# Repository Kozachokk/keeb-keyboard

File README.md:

# keeb-keyboard
Custom keyboard for keeb hackclub

So I built a keyboard from scratch, including the pcb and the case themselves.
I started this project as sort of an introduction to electrical stuff and pcb designing.
During my journey, I learned a lot about pcb designing, wiring, placing vias, creating schematics. I also learned to do keyboard layout, how to use kicad and onshape, where I learned how to create keyboard cases

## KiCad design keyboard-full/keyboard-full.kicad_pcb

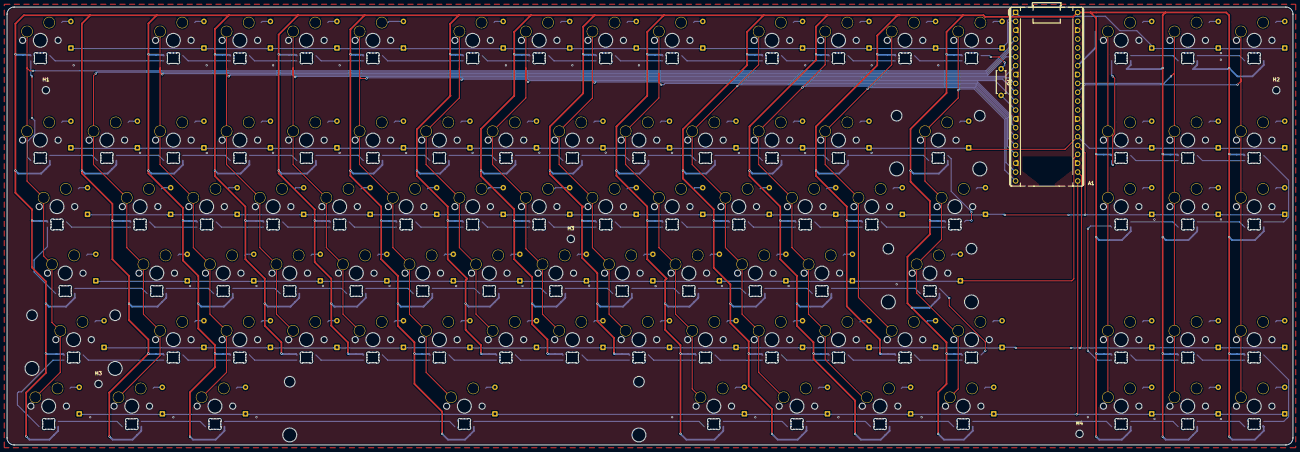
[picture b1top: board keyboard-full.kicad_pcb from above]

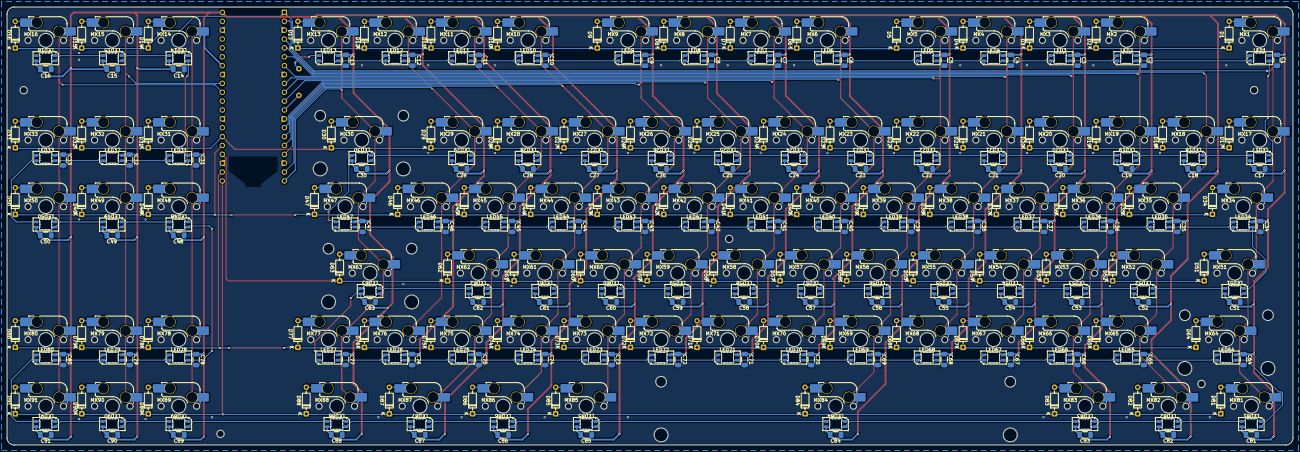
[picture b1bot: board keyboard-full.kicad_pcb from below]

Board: 2 copper layers, 368.3 x 125.4 mm, 375 parts (364 on the bottom side), 208 nets.

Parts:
A1: RaspberryPi_Pico; RaspberryPi_Pico_Common_THT
C1, C2, C3, C4, C5, C6, C7, C8, C9, C10, C11, C12, C13, C14, C15, C16, C17, C18, C19, C20, C21, C22, C23, C24, C25, C26, C27, C28, C29, C30, C31, C32, C33, C34, C35, C36, C37, C38, C39, C40, C41, C42, C43, C44, C45, C46, C47, C48, C49, C50, C51, C52, C53, C54, C55, C56, C57, C58, C59, C60, C61, C62, C63, C64, C65, C66, C67, C68, C69, C70, C71, C72, C73, C74, C75, C76, C77, C78, C79, C80, C81, C82, C83, C84, C85, C86, C87, C88, C89, C90, C91: 0.1uF; C_1206_3216Metric_Pad1.33x1.80mm_HandSolder
D1, D2, D3, D4, D5, D6, D7, D8, D9, D10, D11, D12, D13, D14, D15, D16, D17, D18, D19, D20, D21, D22, D23, D24, D25, D26, D27, D28, D29, D30, D31, D32, D33, D34, D35, D36, D37, D38, D39, D40, D41, D42, D43, D44, D45, D46, D47, D48, D49, D50, D51, D52, D53, D54, D55, D56, D57, D58, D59, D60, D61, D62, D63, D64, D65, D66, D67, D68, D69, D70, D71, D72, D73, D74, D75, D76, D77, D78, D79, D80, D81, D82, D83, D84, D85, D86, D87, D88, D89, D90, D91: 1N4148; D_DO-35_SOD27_P7.62mm_Horizontal
H1, H2, H3, H3#2, H4: MountingHole; MountingHole_2.1mm
LED1, LED2, LED3, LED4, LED5, LED6, LED7, LED8, LED9, LED10, LED11, LED12, LED13, LED14, LED15, LED16, LED17, LED18, LED19, LED20, LED21, LED22, LED23, LED24, LED25, LED26, LED27, LED28, LED29, LED30, LED31, LED32, LED33, LED34, LED35, LED36, LED37, LED38, LED39, LED40, LED41, LED42, LED43, LED44, LED45, LED46, LED47, LED48, LED49, LED50, LED51, LED52, LED53, LED54, LED55, LED56, LED57, LED58, LED59, LED60, LED61, LED62, LED63, LED64, LED65, LED66, LED67, LED68, LED69, LED70, LED71, LED72, LED73, LED74, LED75, LED76, LED77, LED78, LED79, LED80, LED81, LED82, LED83, LED84, LED85, LED86, LED87, LED88, LED89, LED90, LED91: SK6812MINI-E; LED_SK6812MINI-E_3.2x2.8mm_P1.5mm_ReverseMount
MX1, MX2, MX3, MX4, MX5, MX6, MX7, MX8, MX9, MX10, MX11, MX12, MX13, MX14, MX15, MX16, MX17, MX18, MX19, MX20, MX21, MX22, MX23, MX24, MX25, MX26, MX27, MX28, MX29, MX30, MX31, MX32, MX33, MX35, MX36, MX37, MX38, MX39, MX40, MX41, MX42, MX43, MX44, MX45, MX46, MX48, MX49, MX50, MX52, MX53, MX54, MX55, MX56, MX57, MX58, MX59, MX60, MX61, MX62, MX63, MX64, MX65, MX66, MX67, MX68, MX69, MX70, MX71, MX72, MX73, MX74, MX75, MX76, MX77, MX78, MX79, MX80, MX89, MX90, MX91: MX_SW_HS; SW_MX_HS_CPG151101S11_1u
MX34, MX47: MX_SW_HS; SW_MX_HS_CPG151101S11_1.5u
MX51: MX_SW_HS; SW_MX_HS_CPG151101S11_1.75u
MX81, MX82, MX83, MX84, MX85, MX86, MX87, MX88: MX_SW_HS; SW_MX_HS_CPG151101S11_1.25u
R1: R470; R_Axial_DIN0207_L6.3mm_D2.5mm_P7.62mm_Horizontal
S1: MX_stab; STAB_MX_6.25u
S2, S3: MX_stab; STAB_MX_2u
S4: MX_stab; STAB_MX_2.25u

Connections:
+5V: A1.40 (VBUS), C1.1, C2.1, C3.1, C4.1, C5.1, C6.1, C7.1, C8.1, C9.1, C10.1, C11.1, C12.1, C13.1, C14.1, C15.1, C16.1, C17.1, C18.1, C19.1, C20.1, C21.1, C22.1, C23.1, C24.1, C25.1, C26.1, C27.1, C28.1, C29.1, C30.1, C31.1, C32.1, C33.1, C34.1, C35.1, C36.1, C37.1, C38.1, C39.1, C40.1, C41.1, C42.1, C43.1, C44.1, C45.1, C46.1, C47.1, C48.1, C49.1, C50.1, C51.1, C52.1, C53.1, C54.1, C55.1, C56.1, C57.1, C58.1, C59.1, C60.1, C61.1, C62.1, C63.1, C64.1, C65.1, C66.1, C67.1, C68.1, C69.1, C70.1, C71.1, C72.1, C73.1, C74.1, C75.1, C76.1, C77.1, C78.1, C79.1, C80.1, C81.1, C82.1, C83.1, C84.1, C85.1, C86.1, C87.1, C88.1, C89.1, C90.1, C91.1, LED1.3 (VDD), LED2.3 (VDD), LED3.3 (VDD), LED4.3 (VDD), LED5.3 (VDD), LED6.3 (VDD), LED7.3 (VDD), LED8.3 (VDD), LED9.3 (VDD), LED10.3 (VDD), LED11.3 (VDD), LED12.3 (VDD), LED13.3 (VDD), LED14.3 (VDD), LED15.3 (VDD), LED16.3 (VDD), LED17.3 (VDD), LED18.3 (VDD), LED19.3 (VDD), LED20.3 (VDD), LED21.3 (VDD), LED22.3 (VDD), LED23.3 (VDD), LED24.3 (VDD), LED25.3 (VDD), LED26.3 (VDD), LED27.3 (VDD), LED28.3 (VDD), LED29.3 (VDD), LED30.3 (VDD), LED31.3 (VDD), LED32.3 (VDD), LED33.3 (VDD), LED34.3 (VDD), LED35.3 (VDD), LED36.3 (VDD), LED37.3 (VDD), LED38.3 (VDD), LED39.3 (VDD), LED40.3 (VDD), LED41.3 (VDD), LED42.3 (VDD), LED43.3 (VDD), LED44.3 (VDD), LED45.3 (VDD), LED46.3 (VDD), LED47.3 (VDD), LED48.3 (VDD), LED49.3 (VDD), LED50.3 (VDD), LED51.3 (VDD), LED52.3 (VDD), LED53.3 (VDD), LED54.3 (VDD), LED55.3 (VDD), LED56.3 (VDD), LED57.3 (VDD), LED58.3 (VDD), LED59.3 (VDD), LED60.3 (VDD), LED61.3 (VDD), LED62.3 (VDD), LED63.3 (VDD), LED64.3 (VDD), LED65.3 (VDD), LED66.3 (VDD), LED67.3 (VDD), LED68.3 (VDD), LED69.3 (VDD), LED70.3 (VDD), LED71.3 (VDD), LED72.3 (VDD), LED73.3 (VDD), LED74.3 (VDD), LED75.3 (VDD), LED76.3 (VDD), LED77.3 (VDD), LED78.3 (VDD), LED79.3 (VDD), LED80.3 (VDD), LED81.3 (VDD), LED82.3 (VDD), LED83.3 (VDD), LED84.3 (VDD), LED85.3 (VDD), LED86.3 (VDD), LED87.3 (VDD), LED88.3 (VDD), LED89.3 (VDD), LED90.3 (VDD), LED91.3 (VDD)
/Col0: A1.2 (GPIO1), MX1.1, MX17.1, MX34.1, MX51.1, MX64.1, MX81.1
/Col1: A1.4 (GPIO2), MX18.1, MX35.1, MX52.1, MX65.1, MX82.1
/Col2: A1.5 (GPIO3), MX2.1, MX19.1, MX36.1, MX53.1, MX66.1, MX83.1
/Col3: A1.6 (GPIO4), MX3.1, MX20.1, MX37.1, MX54.1, MX67.1
/Col4: A1.7 (GPIO5), MX4.1, MX21.1, MX38.1, MX55.1, MX68.1
/Col5: A1.9 (GPIO6), MX5.1, MX22.1, MX39.1, MX56.1, MX69.1, MX84.1
/Col6: A1.10 (GPIO7), MX6.1, MX23.1, MX40.1, MX57.1, MX70.1
/Col7: A1.11 (GPIO8), MX7.1, MX24.1, MX41.1, MX58.1, MX71.1
/Col8: A1.14 (GPIO10), MX8.1, MX25.1, MX42.1, MX59.1, MX72.1
/Col9: A1.15 (GPIO11), MX9.1, MX26.1, MX43.1, MX60.1, MX73.1, MX85.1
/Col10: A1.16 (GPIO12), MX10.1, MX27.1, MX44.1, MX61.1, MX74.1, MX86.1
/Col11: A1.17 (GPIO13), MX11.1, MX28.1, MX45.1, MX62.1, MX75.1, MX87.1
/Col12: A1.19 (GPIO14), MX12.1, MX29.1, MX46.1, MX76.1
/Col13: A1.20 (GPIO15), MX13.1, MX30.1, MX47.1, MX63.1, MX77.1, MX88.1
/Col14: A1.34 (GPIO28_ADC2), MX14.1, MX31.1, MX48.1, MX78.1, MX89.1
/Col15: A1.32 (GPIO27_ADC1), MX15.1, MX32.1, MX49.1, MX79.1, MX90.1
/Col16: A1.31 (GPIO26_ADC0), MX16.1, MX33.1, MX50.1, MX80.1, MX91.1
/LED: A1.12 (GPIO9), R1.2
/Row0: A1.1 (GPIO0), D1.1 (K), D2.1 (K), D3.1 (K), D4.1 (K), D5.1 (K), D6.1 (K), D7.1 (K), D8.1 (K), D9.1 (K), D10.1 (K), D11.1 (K), D12.1 (K), D13.1 (K), D14.1 (K), D15.1 (K), D16.1 (K)
/Row1: A1.26 (GPIO20), D17.1 (K), D18.1 (K), D19.1 (K), D20.1 (K), D21.1 (K), D22.1 (K), D23.1 (K), D24.1 (K), D25.1 (K), D26.1 (K), D27.1 (K), D28.1 (K), D29.1 (K), D30.1 (K), D31.1 (K), D32.1 (K), D33.1 (K)
/Row2: A1.25 (GPIO19), D34.1 (K), D35.1 (K), D36.1 (K), D37.1 (K), D38.1 (K), D39.1 (K), D40.1 (K), D41.1 (K), D42.1 (K), D43.1 (K), D44.1 (K), D45.1 (K), D46.1 (K), D47.1 (K), D48.1 (K), D49.1 (K), D50.1 (K)
/Row3: A1.24 (GPIO18), D51.1 (K), D52.1 (K), D53.1 (K), D54.1 (K), D55.1 (K), D56.1 (K), D57.1 (K), D58.1 (K), D59.1 (K), D60.1 (K), D61.1 (K), D62.1 (K), D63.1 (K)
/Row4: A1.22 (GPIO17), D64.1 (K), D65.1 (K), D66.1 (K), D67.1 (K), D68.1 (K), D69.1 (K), D70.1 (K), D71.1 (K), D72.1 (K), D73.1 (K), D74.1 (K), D75.1 (K), D76.1 (K), D77.1 (K), D78.1 (K), D79.1 (K), D80.1 (K)
/Row5: A1.21 (GPIO16), D81.1 (K), D82.1 (K), D83.1 (K), D84.1 (K), D85.1 (K), D86.1 (K), D87.1 (K), D88.1 (K), D89.1 (K), D90.1 (K), D91.1 (K)
GND: A1.3 (GND), A1.8 (GND), A1.13 (GND), A1.18 (GND), A1.23 (GND), A1.28 (GND), A1.38 (GND), C1.2, C2.2, C3.2, C4.2, C5.2, C6.2, C7.2, C8.2, C9.2, C10.2, C11.2, C12.2, C13.2, C14.2, C15.2, C16.2, C17.2, C18.2, C19.2, C20.2, C21.2, C22.2, C23.2, C24.2, C26.2, C27.2, C28.2, C29.2, C30.2, C31.2, C32.2, C33.2, C34.2, C35.2, C36.2, C37.2, C38.2, C39.2, C40.2, C41.2, C42.2, C43.2, C44.2, C45.2, C46.2, C47.2, C48.2, C49.2, C50.2, C51.2, C52.2, C53.2, C54.2, C55.2, C56.2, C57.2, C58.2, C59.2, C60.2, C61.2, C62.2, C63.2, C64.2, C65.2, C66.2, C67.2, C68.2, C69.2, C70.2, C71.2, C72.2, C73.2, C74.2, C75.2, C76.2, C77.2, C78.2, C79.2, C80.2, C81.2, C82.2, C83.2, C84.2, C85.2, C86.2, C87.2, C88.2, C89.2, C90.2, C91.2, LED1.1 (VSS), LED2.1 (VSS), LED3.1 (VSS), LED4.1 (VSS), LED5.1 (VSS), LED6.1 (VSS), LED7.1 (VSS), LED8.1 (VSS), LED9.1 (VSS), LED10.1 (VSS), LED11.1 (VSS), LED12.1 (VSS), LED13.1 (VSS), LED14.1 (VSS), LED15.1 (VSS), LED16.1 (VSS), LED17.1 (VSS), LED18.1 (VSS), LED19.1 (VSS), LED20.1 (VSS), LED21.1 (VSS), LED22.1 (VSS), LED23.1 (VSS), LED24.1 (VSS), LED25.1 (VSS), LED26.1 (VSS), LED27.1 (VSS), LED28.1 (VSS), LED29.1 (VSS), LED30.1 (VSS), LED31.1 (VSS), LED32.1 (VSS), LED33.1 (VSS), LED34.1 (VSS), LED35.1 (VSS), LED36.1 (VSS), LED37.1 (VSS), LED38.1 (VSS), LED39.1 (VSS), LED40.1 (VSS), LED41.1 (VSS), LED42.1 (VSS), LED43.1 (VSS), LED44.1 (VSS), LED45.1 (VSS), LED46.1 (VSS), LED47.1 (VSS), LED48.1 (VSS), LED49.1 (VSS), LED50.1 (VSS), LED51.1 (VSS), LED52.1 (VSS), LED53.1 (VSS), LED54.1 (VSS), LED55.1 (VSS), LED56.1 (VSS), LED57.1 (VSS), LED58.1 (VSS), LED59.1 (VSS), LED60.1 (VSS), LED61.1 (VSS), LED62.1 (VSS), LED63.1 (VSS), LED64.1 (VSS), LED65.1 (VSS), LED66.1 (VSS), LED67.1 (VSS), LED68.1 (VSS), LED69.1 (VSS), LED70.1 (VSS), LED71.1 (VSS), LED72.1 (VSS), LED73.1 (VSS), LED74.1 (VSS), LED75.1 (VSS), LED76.1 (VSS), LED77.1 (VSS), LED78.1 (VSS), LED79.1 (VSS), LED80.1 (VSS), LED81.1 (VSS), LED82.1 (VSS), LED83.1 (VSS), LED84.1 (VSS), LED85.1 (VSS), LED86.1 (VSS), LED87.1 (VSS), LED88.1 (VSS), LED89.1 (VSS), LED90.1 (VSS), LED91.1 (VSS)
unnamed: D1.2 (A), MX1.2
unnamed: D2.2 (A), MX2.2
unnamed: D3.2 (A), MX3.2
unnamed: D4.2 (A), MX4.2
unnamed: D5.2 (A), MX5.2
unnamed: D6.2 (A), MX6.2
unnamed: D7.2 (A), MX7.2
unnamed: D8.2 (A), MX8.2
unnamed: D9.2 (A), MX9.2
unnamed: D10.2 (A), MX10.2
unnamed: D11.2 (A), MX11.2
unnamed: D12.2 (A), MX12.2
unnamed: D13.2 (A), MX13.2
unnamed: D14.2 (A), MX14.2
unnamed: D15.2 (A), MX15.2
unnamed: D16.2 (A), MX16.2
unnamed: D17.2 (A), MX17.2
unnamed: D18.2 (A), MX18.2
unnamed: D19.2 (A), MX19.2
unnamed: D20.2 (A), MX20.2
unnamed: D21.2 (A), MX21.2
unnamed: D22.2 (A), MX22.2
unnamed: D23.2 (A), MX23.2
unnamed: D24.2 (A), MX24.2
unnamed: D25.2 (A), MX25.2
unnamed: D26.2 (A), MX26.2
unnamed: D27.2 (A), MX27.2
unnamed: D28.2 (A), MX28.2
unnamed: D29.2 (A), MX29.2
unnamed: D30.2 (A), MX30.2
unnamed: D31.2 (A), MX31.2
unnamed: D32.2 (A), MX32.2
unnamed: D33.2 (A), MX33.2
unnamed: D34.2 (A), MX34.2
unnamed: D35.2 (A), MX35.2
unnamed: D36.2 (A), MX36.2
unnamed: D37.2 (A), MX37.2
unnamed: D38.2 (A), MX38.2
unnamed: D39.2 (A), MX39.2
unnamed: D40.2 (A), MX40.2
unnamed: D41.2 (A), MX41.2
unnamed: D42.2 (A), MX42.2
unnamed: D43.2 (A), MX43.2
unnamed: D44.2 (A), MX44.2
unnamed: D45.2 (A), MX45.2
unnamed: D46.2 (A), MX46.2
unnamed: D47.2 (A), MX47.2
unnamed: D48.2 (A), MX48.2
unnamed: D49.2 (A), MX49.2
unnamed: D50.2 (A), MX50.2
unnamed: D51.2 (A), MX51.2
unnamed: D52.2 (A), MX52.2
unnamed: D53.2 (A), MX53.2
unnamed: D54.2 (A), MX54.2
unnamed: D55.2 (A), MX55.2
unnamed: D56.2 (A), MX56.2
unnamed: D57.2 (A), MX57.2
unnamed: D58.2 (A), MX58.2
unnamed: D59.2 (A), MX59.2
unnamed: D60.2 (A), MX60.2
unnamed: D61.2 (A), MX61.2
unnamed: D62.2 (A), MX62.2
unnamed: D63.2 (A), MX63.2
unnamed: D64.2 (A), MX64.2
unnamed: D65.2 (A), MX65.2
unnamed: D66.2 (A), MX66.2
unnamed: D67.2 (A), MX67.2
unnamed: D68.2 (A), MX68.2
unnamed: D69.2 (A), MX69.2
unnamed: D70.2 (A), MX70.2
unnamed: D71.2 (A), MX71.2
unnamed: D72.2 (A), MX72.2
unnamed: D73.2 (A), MX73.2
unnamed: D74.2 (A), MX74.2
unnamed: D75.2 (A), MX75.2
unnamed: D76.2 (A), MX76.2
unnamed: D77.2 (A), MX77.2
unnamed: D78.2 (A), MX78.2
unnamed: D79.2 (A), MX79.2
unnamed: D80.2 (A), MX80.2
unnamed: D81.2 (A), MX81.2
unnamed: D82.2 (A), MX82.2
unnamed: D83.2 (A), MX83.2
unnamed: D84.2 (A), MX84.2
unnamed: D85.2 (A), MX85.2
unnamed: D86.2 (A), MX86.2
unnamed: D87.2 (A), MX87.2
unnamed: D88.2 (A), MX88.2
unnamed: D89.2 (A), MX89.2
unnamed: D90.2 (A), MX90.2
unnamed: D91.2 (A), MX91.2
unnamed: LED1.2 (DIN), LED2.4 (DOUT)
unnamed: LED1.4 (DOUT), LED17.2 (DIN)
unnamed: LED2.2 (DIN), LED3.4 (DOUT)
unnamed: LED3.2 (DIN), LED4.4 (DOUT)
unnamed: LED4.2 (DIN), LED5.4 (DOUT)
unnamed: LED5.2 (DIN), LED6.4 (DOUT)
unnamed: LED6.2 (DIN), LED7.4 (DOUT)
unnamed: LED7.2 (DIN), LED8.4 (DOUT)
unnamed: LED8.2 (DIN), LED9.4 (DOUT)
unnamed: LED10.2 (DIN), LED11.4 (DOUT)
unnamed: LED9.2 (DIN), LED10.4 (DOUT)
unnamed: LED11.2 (DIN), LED12.4 (DOUT)
unnamed: LED12.2 (DIN), LED13.4 (DOUT)
unnamed: LED13.2 (DIN), R1.1
unnamed: LED14.2 (DIN), LED31.4 (DOUT)
unnamed: LED14.4 (DOUT), LED15.2 (DIN)
unnamed: LED15.4 (DOUT), LED16.2 (DIN)
unnamed: LED17.4 (DOUT), LED18.2 (DIN)
unnamed: LED18.4 (DOUT), LED19.2 (DIN)
unnamed: LED19.4 (DOUT), LED20.2 (DIN)
unnamed: LED20.4 (DOUT), LED21.2 (DIN)
unnamed: LED21.4 (DOUT), LED22.2 (DIN)
unnamed: LED22.4 (DOUT), LED23.2 (DIN)
unnamed: LED23.4 (DOUT), LED24.2 (DIN)
unnamed: LED24.4 (DOUT), LED25.2 (DIN)
unnamed: LED25.4 (DOUT), LED26.2 (DIN)
unnamed: LED26.4 (DOUT), LED27.2 (DIN)
unnamed: LED27.4 (DOUT), LED28.2 (DIN)
unnamed: LED28.4 (DOUT), LED29.2 (DIN)
unnamed: LED29.4 (DOUT), LED30.2 (DIN)
unnamed: LED30.4 (DOUT), LED47.2 (DIN)
unnamed: LED31.2 (DIN), LED32.4 (DOUT)
unnamed: LED32.2 (DIN), LED33.4 (DOUT)
unnamed: LED33.2 (DIN), LED50.4 (DOUT)
unnamed: LED34.2 (DIN), LED35.4 (DOUT)
unnamed: LED34.4 (DOUT), LED51.2 (DIN)
unnamed: LED35.2 (DIN), LED36.4 (DOUT)
unnamed: LED36.2 (DIN), LED37.4 (DOUT)
unnamed: LED37.2 (DIN), LED38.4 (DOUT)
unnamed: LED38.2 (DIN), LED39.4 (DOUT)
unnamed: LED39.2 (DIN), LED40.4 (DOUT)
unnamed: LED40.2 (DIN), LED41.4 (DOUT)
unnamed: LED41.2 (DIN), LED42.4 (DOUT)
unnamed: LED42.2 (DIN), LED43.4 (DOUT)
unnamed: LED43.2 (DIN), LED44.4 (DOUT)
unnamed: LED44.2 (DIN), LED45.4 (DOUT)
unnamed: LED45.2 (DIN), LED46.4 (DOUT)
unnamed: LED46.2 (DIN), LED47.4 (DOUT)
unnamed: LED48.2 (DIN), LED78.4 (DOUT)
unnamed: LED48.4 (DOUT), LED49.2 (DIN)
unnamed: LED49.4 (DOUT), LED50.2 (DIN)
unnamed: LED51.4 (DOUT), LED52.2 (DIN)
unnamed: LED52.4 (DOUT), LED53.2 (DIN)
unnamed: LED53.4 (DOUT), LED54.2 (DIN)
unnamed: LED54.4 (DOUT), LED55.2 (DIN)
unnamed: LED55.4 (DOUT), LED56.2 (DIN)
unnamed: LED56.4 (DOUT), LED57.2 (DIN)
unnamed: LED57.4 (DOUT), LED58.2 (DIN)
unnamed: LED58.4 (DOUT), LED59.2 (DIN)
unnamed: LED59.4 (DOUT), LED60.2 (DIN)
unnamed: LED60.4 (DOUT), LED61.2 (DIN)
unnamed: LED61.4 (DOUT), LED62.2 (DIN)
unnamed: LED62.4 (DOUT), LED63.2 (DIN)
unnamed: LED63.4 (DOUT), LED77.2 (DIN)
unnamed: LED64.2 (DIN), LED65.4 (DOUT)
unnamed: LED64.4 (DOUT), LED81.2 (DIN)
unnamed: LED65.2 (DIN), LED66.4 (DOUT)
unnamed: LED66.2 (DIN), LED67.4 (DOUT)
unnamed: LED67.2 (DIN), LED68.4 (DOUT)
unnamed: LED68.2 (DIN), LED69.4 (DOUT)
unnamed: LED69.2 (DIN), LED70.4 (DOUT)
unnamed: LED70.2 (DIN), LED71.4 (DOUT)
unnamed: LED71.2 (DIN), LED72.4 (DOUT)
unnamed: LED72.2 (DIN), LED73.4 (DOUT)
unnamed: LED73.2 (DIN), LED74.4 (DOUT)
unnamed: LED74.2 (DIN), LED75.4 (DOUT)
unnamed: LED75.2 (DIN), LED76.4 (DOUT)
unnamed: LED76.2 (DIN), LED77.4 (DOUT)
unnamed: LED78.2 (DIN), LED79.4 (DOUT)
unnamed: LED79.2 (DIN), LED80.4 (DOUT)
unnamed: LED80.2 (DIN), LED91.4 (DOUT)
unnamed: LED81.4 (DOUT), LED82.2 (DIN)
unnamed: LED82.4 (DOUT), LED83.2 (DIN)
unnamed: LED83.4 (DOUT), LED84.2 (DIN)
unnamed: LED84.4 (DOUT), LED85.2 (DIN)
unnamed: LED85.4 (DOUT), LED86.2 (DIN)
unnamed: LED86.4 (DOUT), LED87.2 (DIN)
unnamed: LED87.4 (DOUT), LED88.2 (DIN)
unnamed: LED88.4 (DOUT), LED89.2 (DIN)
unnamed: LED89.4 (DOUT), LED90.2 (DIN)
unnamed: LED90.4 (DOUT), LED91.2 (DIN)

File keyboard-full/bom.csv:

Id;Designator;Footprint;Quantity;Designation;Supplier and ref;
1;A1;RaspberryPi_Pico_Common_THT;1;RaspberryPi_Pico;https://orpheuspico.hackclub.com/;
2;C1, C2, C3, C4, C5, C6, C7, C8, C9, C10, C11, C12, C13, C14, C15, C16, C17, C18, C19, C20, C21, C22, C23, C24, C25, C26, C27, C28, C29, C30, C31, C32, C33, C34, C35, C36, C37, C38, C39, C40, C41, C42, C43, C44, C45, C46, C47, C48, C49, C50, C51, C52, C53, C54, C55, C56, C57, C58, C59, C60, C61, C62, C63, C64, C65, C66, C67, C68, C69, C70, C71, C72, C73, C74, C75, C76, C77, C78, C79, C80, C81, C82, C83, C84, C85, C86, C87, C88, C89, C90, C91;C_1206_3216Metric_Pad1.33x1.80mm_HandSolder;91;0.1uF;https://www.digikey.ca/en/products/detail/w%C3%BCrth-elektro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;
3;D1, D2, D3, D4, D5, D6, D7, D8, D9, D10, D11, D12, D13, D14, D15, D16, D17, D18, D19, D20, D21, D22, D23, D24, D25, D26, D27, D28, D29, D30, D31, D32, D33, D34, D35, D36, D37, D38, D39, D40, D41, D42, D43, D44, D45, D46, D47, D48, D49, D50, D51, D52, D53, D54, D55, D56, D57, D58, D59, D60, D61, D62, D63, D64, D65, D66, D67, D68, D69, D70, D71, D72, D73, D74, D75, D76, D77, D78, D79, D80, D81, D82, D83, D84, D85, D86, D87, D88, D89, D90, D91;D_DO-35_SOD27_P7.62mm_Horizontal;91;1N4148;https://www.aliexpress.com/item/1005008195178693.html?spm=a2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;
4;LED1, LED2, LED3, LED4, LED5, LED6, LED7, LED8, LED9, LED10, LED11, LED12, LED13, LED14, LED15, LED16, LED17, LED18, LED19, LED20, LED21, LED22, LED23, LED24, LED25, LED26, LED27, LED28, LED29, LED30, LED31, LED32, LED33, LED34, LED35, LED36, LED37, LED38, LED39, LED40, LED41, LED42, LED43, LED44, LED45, LED46, LED47, LED48, LED49, LED50, LED51, LED52, LED53, LED54, LED55, LED56, LED57, LED58, LED59, LED60, LED61, LED62, LED63, LED64, LED65, LED66, LED67, LED68, LED69, LED70, LED71, LED72, LED73, LED74, LED75, LED76, LED77, LED78, LED79, LED80, LED81, LED82, LED83, LED84, LED85, LED86, LED87, LED88, LED89, LED90, LED91;LED_SK6812MINI-E_3.2x2.8mm_P1.5mm_ReverseMount;91;SK6812MINI-E;https://www.lcsc.com/product-detail/C5149201.html?s_z=n_SK68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;
5;MX1, MX2, MX3, MX4, MX5, MX6, MX7, MX8, MX9, MX10, MX11, MX12, MX13, MX14, MX15, MX16, MX17, MX18, MX19, MX20, MX21, MX22, MX23, MX24, MX25, MX26, MX27, MX28, MX29, MX30, MX31, MX32, MX33, MX35, MX36, MX37, MX38, MX39, MX40, MX41, MX42, MX43, MX44, MX45, MX46, MX48, MX49, MX50, MX52, MX53, MX54, MX55, MX56, MX57, MX58, MX59, MX60, MX61, MX62, MX63, MX64, MX65, MX66, MX67, MX68, MX69, MX70, MX71, MX72, MX73, MX74, MX75, MX76, MX77, MX78, MX79, MX80, MX89, MX90, MX91;SW_MX_HS_CPG151101S11_1u;80;MX_SW_HS;https://www.aliexpress.com/item/1005007232040760.html?spm=a2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;Choose the CGP151101S11 option(Type A)
6;MX34, MX47;SW_MX_HS_CPG151101S11_1.5u;2;MX_SW_HS;https://www.aliexpress.com/item/1005007232040760.html?spm=a2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;Choose the CGP151101S11 option(Type A)
7;MX51;SW_MX_HS_CPG151101S11_1.75u;1;MX_SW_HS;https://www.aliexpress.com/item/1005007232040760.html?spm=a2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;Choose the CGP151101S11 option(Type A)
8;MX81, MX82, MX83, MX84, MX85, MX86, MX87, MX88;SW_MX_HS_CPG151101S11_1.25u;8;MX_SW_HS;https://www.aliexpress.com/item/1005007232040760.html?spm=a2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;Choose the CGP151101S11 option(Type A)
9;R1;R_Axial_DIN0207_L6.3mm_D2.5mm_P7.62mm_Horizontal;1;R470;;
10;S1;STAB_MX_6.25u;1;MX_stab;https://www.aliexpress.com/item/1005010788206824.html?spm=a2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;
11;S2, S3;STAB_MX_2u;2;MX_stab;https://www.aliexpress.com/item/1005010788206824.html?spm=a2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;
12;S4;STAB_MX_2.25u;1;MX_stab;https://www.aliexpress.com/item/1005010788206824.html?spm=a2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;

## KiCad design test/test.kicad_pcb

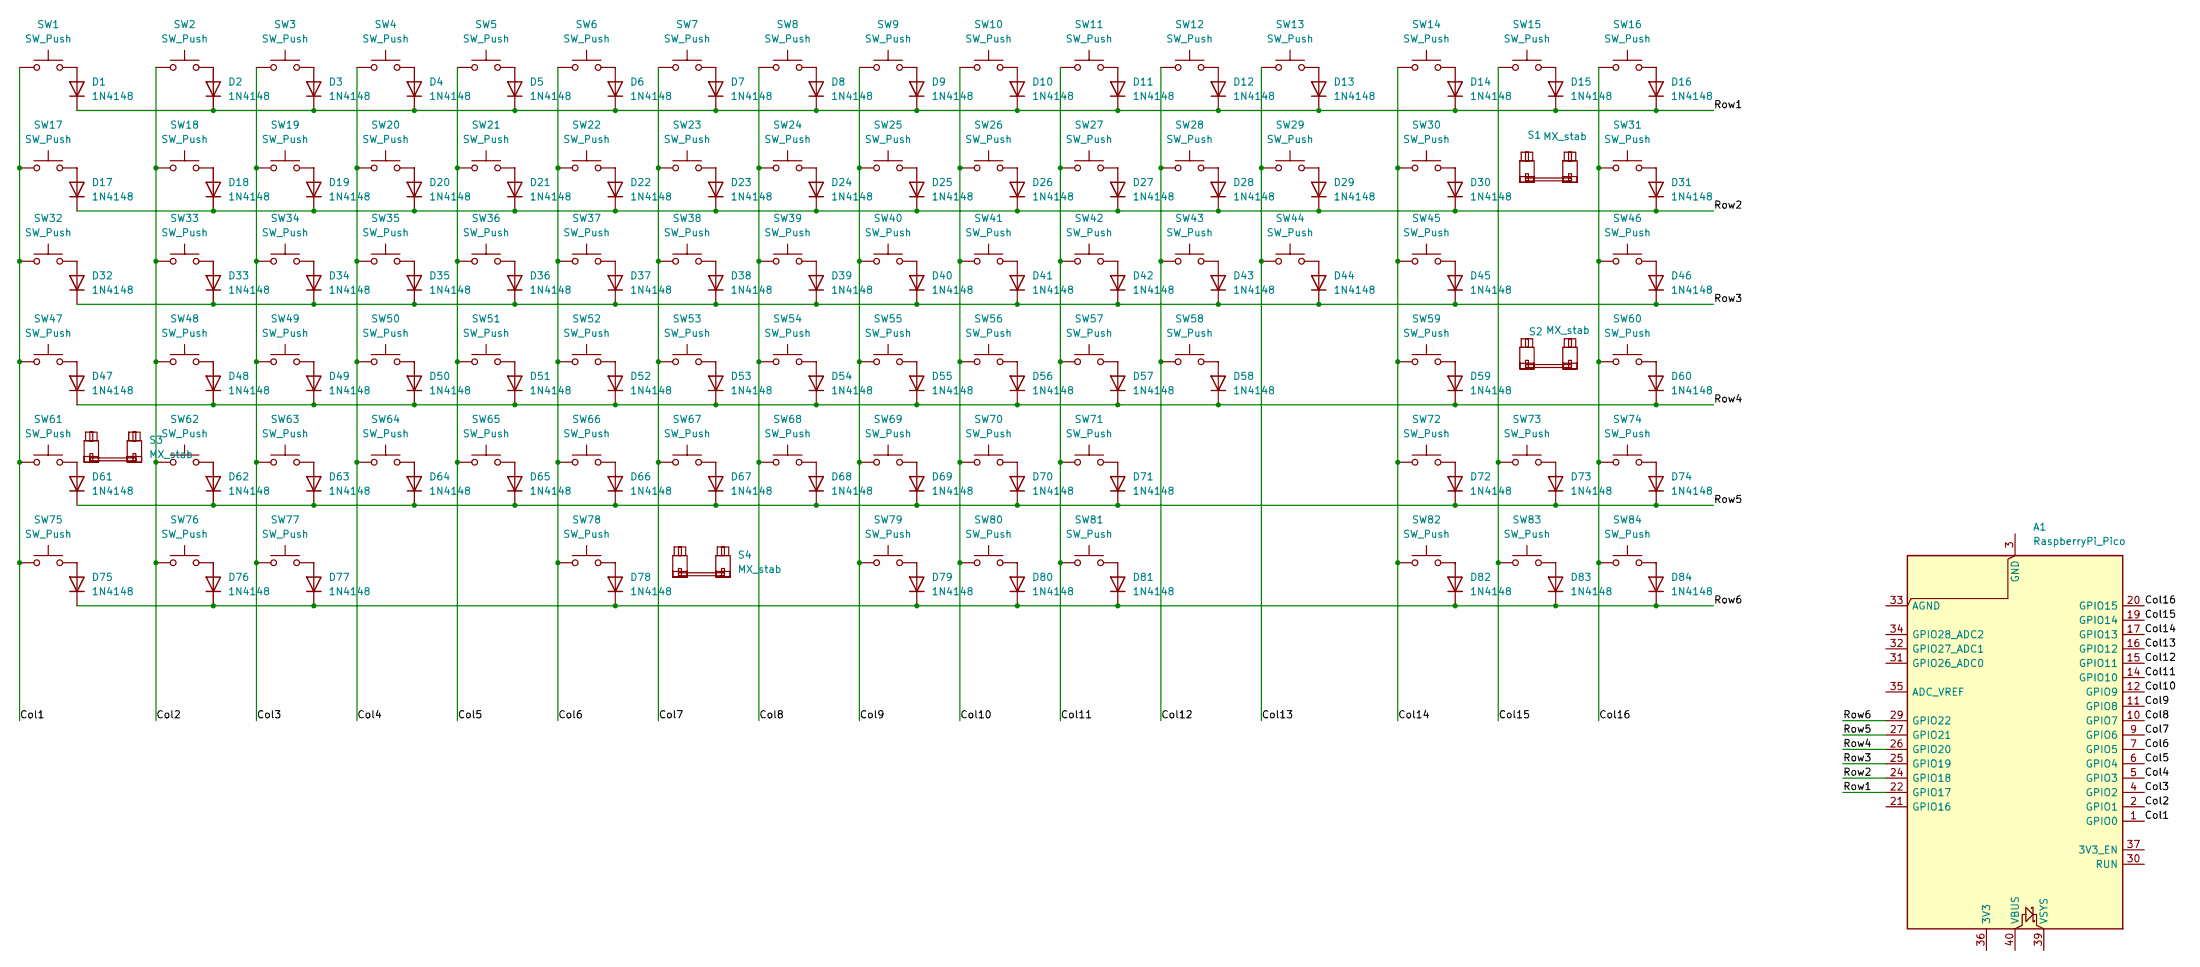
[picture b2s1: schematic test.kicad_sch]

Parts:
A1: RaspberryPi_Pico; RaspberryPi_Pico_Common_THT
D1, D2, D3, D4, D5, D6, D7, D8, D9, D10, D11, D12, D13, D14, D15, D16, D17, D18, D19, D20, D21, D22, D23, D24, D25, D26, D27, D28, D29, D30, D31, D32, D33, D34, D35, D36, D37, D38, D39, D40, D41, D42, D43, D44, D45, D46, D47, D48, D49, D50, D51, D52, D53, D54, D55, D56, D57, D58, D59, D60, D61, D62, D63, D64, D65, D66, D67, D68, D69, D70, D71, D72, D73, D74, D75, D76, D77, D78, D79, D80, D81, D82, D83, D84: 1N4148; D_DO-35_SOD27_P7.62mm_Horizontal
S1: MX_stab; STAB_MX_2u
S2, S3: MX_stab; STAB_MX_2.25u
S4: MX_stab; STAB_MX_5u
SW1, SW2, SW3, SW4, SW5, SW6, SW7, SW8, SW9, SW10, SW11, SW12, SW13, SW14, SW15, SW16, SW17, SW18, SW19, SW20, SW21, SW22, SW23, SW24, SW25, SW26, SW27, SW28, SW29, SW30, SW31, SW32, SW33, SW34, SW35, SW36, SW37, SW38, SW39, SW40, SW41, SW42, SW43, SW44, SW45, SW46, SW47, SW48, SW49, SW50, SW51, SW52, SW53, SW54, SW55, SW56, SW57, SW58, SW59, SW60, SW61, SW62, SW63, SW64, SW65, SW66, SW67, SW68, SW69, SW70, SW71, SW72, SW73, SW74, SW75, SW76, SW77, SW78, SW79, SW80, SW81, SW82, SW83, SW84: SW_Push; SW_MX_1u

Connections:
/Col1: A1.1 (GPIO0), SW1.1, SW17.1, SW32.1, SW47.1, SW61.1, SW75.1
/Col2: A1.2 (GPIO1), SW2.1, SW18.1, SW33.1, SW48.1, SW62.1, SW76.1
/Col3: A1.4 (GPIO2), SW3.1, SW19.1, SW34.1, SW49.1, SW63.1, SW77.1
/Col4: A1.5 (GPIO3), SW4.1, SW20.1, SW35.1, SW50.1, SW64.1
/Col5: A1.6 (GPIO4), SW5.1, SW21.1, SW36.1, SW51.1, SW65.1
/Col6: A1.7 (GPIO5), SW6.1, SW22.1, SW37.1, SW52.1, SW66.1, SW78.1
/Col7: A1.9 (GPIO6), SW7.1, SW23.1, SW38.1, SW53.1, SW67.1
/Col8: A1.10 (GPIO7), SW8.1, SW24.1, SW39.1, SW54.1, SW68.1
/Col9: A1.11 (GPIO8), SW9.1, SW25.1, SW40.1, SW55.1, SW69.1, SW79.1
/Col10: A1.12 (GPIO9), SW10.1, SW26.1, SW41.1, SW56.1, SW70.1, SW80.1
/Col11: A1.14 (GPIO10), SW11.1, SW27.1, SW42.1, SW57.1, SW71.1, SW81.1
/Col12: A1.15 (GPIO11), SW12.1, SW28.1, SW43.1, SW58.1
/Col13: A1.16 (GPIO12), SW13.1, SW29.1, SW44.1
/Col14: A1.17 (GPIO13), SW14.1, SW30.1, SW45.1, SW59.1, SW72.1, SW82.1
/Col15: A1.19 (GPIO14), SW15.1, SW73.1, SW83.1
/Col16: A1.20 (GPIO15), SW16.1, SW31.1, SW46.1, SW60.1, SW74.1, SW84.1
/Row1: A1.22 (GPIO17), D1.1 (K), D2.1 (K), D3.1 (K), D4.1 (K), D5.1 (K), D6.1 (K), D7.1 (K), D8.1 (K), D9.1 (K), D10.1 (K), D11.1 (K), D12.1 (K), D13.1 (K), D14.1 (K), D15.1 (K), D16.1 (K)
/Row2: A1.24 (GPIO18), D17.1 (K), D18.1 (K), D19.1 (K), D20.1 (K), D21.1 (K), D22.1 (K), D23.1 (K), D24.1 (K), D25.1 (K), D26.1 (K), D27.1 (K), D28.1 (K), D29.1 (K), D30.1 (K), D31.1 (K)
/Row3: A1.25 (GPIO19), D32.1 (K), D33.1 (K), D34.1 (K), D35.1 (K), D36.1 (K), D37.1 (K), D38.1 (K), D39.1 (K), D40.1 (K), D41.1 (K), D42.1 (K), D43.1 (K), D44.1 (K), D45.1 (K), D46.1 (K)
/Row4: A1.26 (GPIO20), D47.1 (K), D48.1 (K), D49.1 (K), D50.1 (K), D51.1 (K), D52.1 (K), D53.1 (K), D54.1 (K), D55.1 (K), D56.1 (K), D57.1 (K), D58.1 (K), D59.1 (K), D60.1 (K)
/Row5: A1.27 (GPIO21), D61.1 (K), D62.1 (K), D63.1 (K), D64.1 (K), D65.1 (K), D66.1 (K), D67.1 (K), D68.1 (K), D69.1 (K), D70.1 (K), D71.1 (K), D72.1 (K), D73.1 (K), D74.1 (K)
/Row6: A1.29 (GPIO22), D75.1 (K), D76.1 (K), D77.1 (K), D78.1 (K), D79.1 (K), D80.1 (K), D81.1 (K), D82.1 (K), D83.1 (K), D84.1 (K)
unnamed: A1.3 (GND), A1.8 (GND), A1.13 (GND), A1.18 (GND), A1.23 (GND), A1.28 (GND), A1.38 (GND)
unnamed: D1.2 (A), SW1.2
unnamed: D2.2 (A), SW2.2
unnamed: D3.2 (A), SW3.2
unnamed: D4.2 (A), SW4.2
unnamed: D5.2 (A), SW5.2
unnamed: D6.2 (A), SW6.2
unnamed: D7.2 (A), SW7.2
unnamed: D8.2 (A), SW8.2
unnamed: D9.2 (A), SW9.2
unnamed: D10.2 (A), SW10.2
unnamed: D11.2 (A), SW11.2
unnamed: D12.2 (A), SW12.2
unnamed: D13.2 (A), SW13.2
unnamed: D14.2 (A), SW14.2
unnamed: D15.2 (A), SW15.2
unnamed: D16.2 (A), SW16.2
unnamed: D17.2 (A), SW17.2
unnamed: D18.2 (A), SW18.2
unnamed: D19.2 (A), SW19.2
unnamed: D20.2 (A), SW20.2
unnamed: D21.2 (A), SW21.2
unnamed: D22.2 (A), SW22.2
unnamed: D23.2 (A), SW23.2
unnamed: D24.2 (A), SW24.2
unnamed: D25.2 (A), SW25.2
unnamed: D26.2 (A), SW26.2
unnamed: D27.2 (A), SW27.2
unnamed: D28.2 (A), SW28.2
unnamed: D29.2 (A), SW29.2
unnamed: D30.2 (A), SW30.2
unnamed: D31.2 (A), SW31.2
unnamed: D32.2 (A), SW32.2
unnamed: D33.2 (A), SW33.2
unnamed: D34.2 (A), SW34.2
unnamed: D35.2 (A), SW35.2
unnamed: D36.2 (A), SW36.2
unnamed: D37.2 (A), SW37.2
unnamed: D38.2 (A), SW38.2
unnamed: D39.2 (A), SW39.2
unnamed: D40.2 (A), SW40.2
unnamed: D41.2 (A), SW41.2
unnamed: D42.2 (A), SW42.2
unnamed: D43.2 (A), SW43.2
unnamed: D44.2 (A), SW44.2
unnamed: D45.2 (A), SW45.2
unnamed: D46.2 (A), SW46.2
unnamed: D47.2 (A), SW47.2
unnamed: D48.2 (A), SW48.2
unnamed: D49.2 (A), SW49.2
unnamed: D50.2 (A), SW50.2
unnamed: D51.2 (A), SW51.2
unnamed: D52.2 (A), SW52.2
unnamed: D53.2 (A), SW53.2
unnamed: D54.2 (A), SW54.2
unnamed: D55.2 (A), SW55.2
unnamed: D56.2 (A), SW56.2
unnamed: D57.2 (A), SW57.2
unnamed: D58.2 (A), SW58.2
unnamed: D59.2 (A), SW59.2
unnamed: D60.2 (A), SW60.2
unnamed: D61.2 (A), SW61.2
unnamed: D62.2 (A), SW62.2
unnamed: D63.2 (A), SW63.2
unnamed: D64.2 (A), SW64.2
unnamed: D65.2 (A), SW65.2
unnamed: D66.2 (A), SW66.2
unnamed: D67.2 (A), SW67.2
unnamed: D68.2 (A), SW68.2
unnamed: D69.2 (A), SW69.2
unnamed: D70.2 (A), SW70.2
unnamed: D71.2 (A), SW71.2
unnamed: D72.2 (A), SW72.2
unnamed: D73.2 (A), SW73.2
unnamed: D74.2 (A), SW74.2
unnamed: D75.2 (A), SW75.2
unnamed: D76.2 (A), SW76.2
unnamed: D77.2 (A), SW77.2
unnamed: D78.2 (A), SW78.2
unnamed: D79.2 (A), SW79.2
unnamed: D80.2 (A), SW80.2
unnamed: D81.2 (A), SW81.2
unnamed: D82.2 (A), SW82.2
unnamed: D83.2 (A), SW83.2
unnamed: D84.2 (A), SW84.2

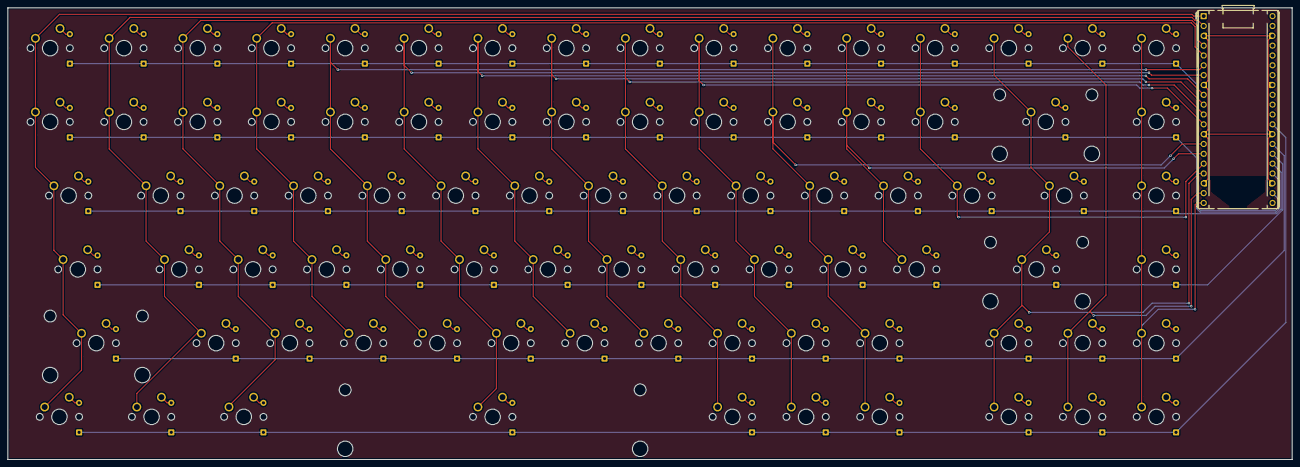
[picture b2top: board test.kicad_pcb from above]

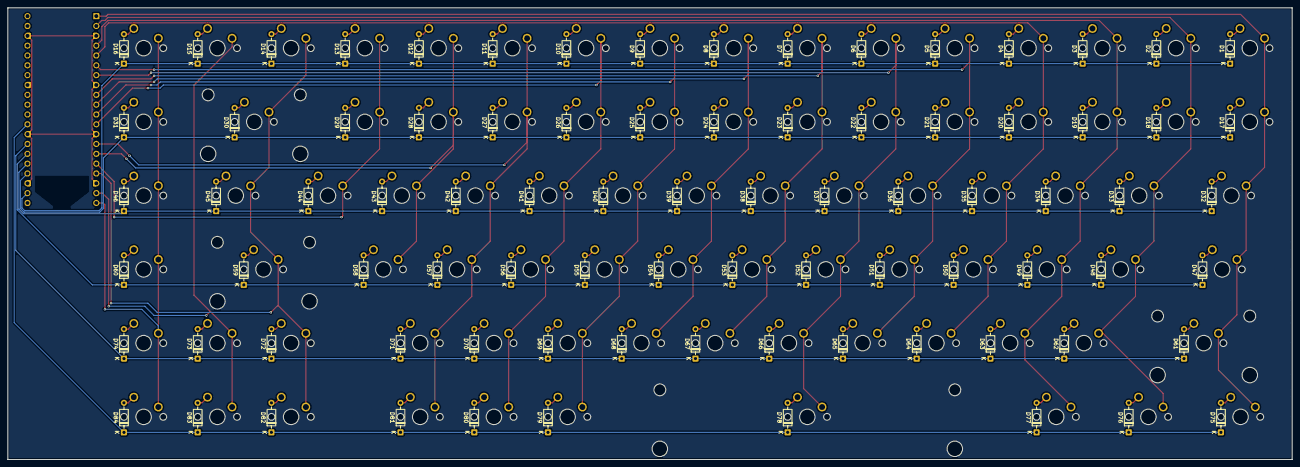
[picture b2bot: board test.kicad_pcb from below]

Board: 2 copper layers, 331.8 x 116.7 mm, 173 parts (84 on the bottom side), 107 nets.
